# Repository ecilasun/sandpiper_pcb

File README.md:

## Sandpiper keyboard PCB and enclosure design files

This repo contains the PCB files for sandpiper project.

## Notes

- This PCB is optional and is not required to be able to run sandpiper. It merely contains a custom USB keyboard that fits into the provided enclosure.
- The enclosure is also optional. Sandpiper does not requre an enclosure to function and can be booted from pretty much any Xynq7020 board with 512Mbytes of memory, an etnernet and USB controller, plus some HDMI connector leading to the FPGA pins. For boards with more memory than 512Mbytes the device tree and SDK has to be updated to shift device addresses to the last 32Mbytes of memory. This also means th driver has to be rebuilt with those addresses (in the future driver will read them from the devic tree so there won't be a need to rebuild it)
- The enclosure is designed to be printed in one big piece for the top and bottom halves (plus the side connection pieces) Recommended material is PETG-strong as it is very unlikely to warp. Other materials might also work but print at your own risk or split the design manually, as there's no built-in measures in the design to avoid warping.
- Enclosure design requires solidworks connected, and the pcb design required KiCad 9 or above.
- If you intend to build a PCB yourself via online services (oshpark, jlcpcb etc) please note to match the parts to the ones listed as close as you can. Mismatches in part numbers might result in wrong pin connections.
- If you build the keyboard PCB and want to program the firmware on it, please see the firmware/ folder in this repo. Use an AVR programmer with AVRdude / AVRdudess or QMK Toolbox to burn the flash onto the chip.
- The pin header for the programmer goes on the bottom side of the board where the chip sits, and the square pin connection is actually the MISO pin and not the ground pin due to an error. Please see the following image to locate the correct pins and plug the programmer header accordingly:<br><br>
- Do not forget to cut or remove the programming header pins once you're done so that the board does not get stuck or bend when sliding it into the rails on the bottom side of the enclosure.

## Documentation

See the [Sandpiper project page](https://ecilasun.github.io/sandpiper/) for links to all related repositories and SDK documentation.

## Development toolchains

See the [Sandpiper project page](https://ecilasun.github.io/sandpiper/) for development toolchain setup instructions.

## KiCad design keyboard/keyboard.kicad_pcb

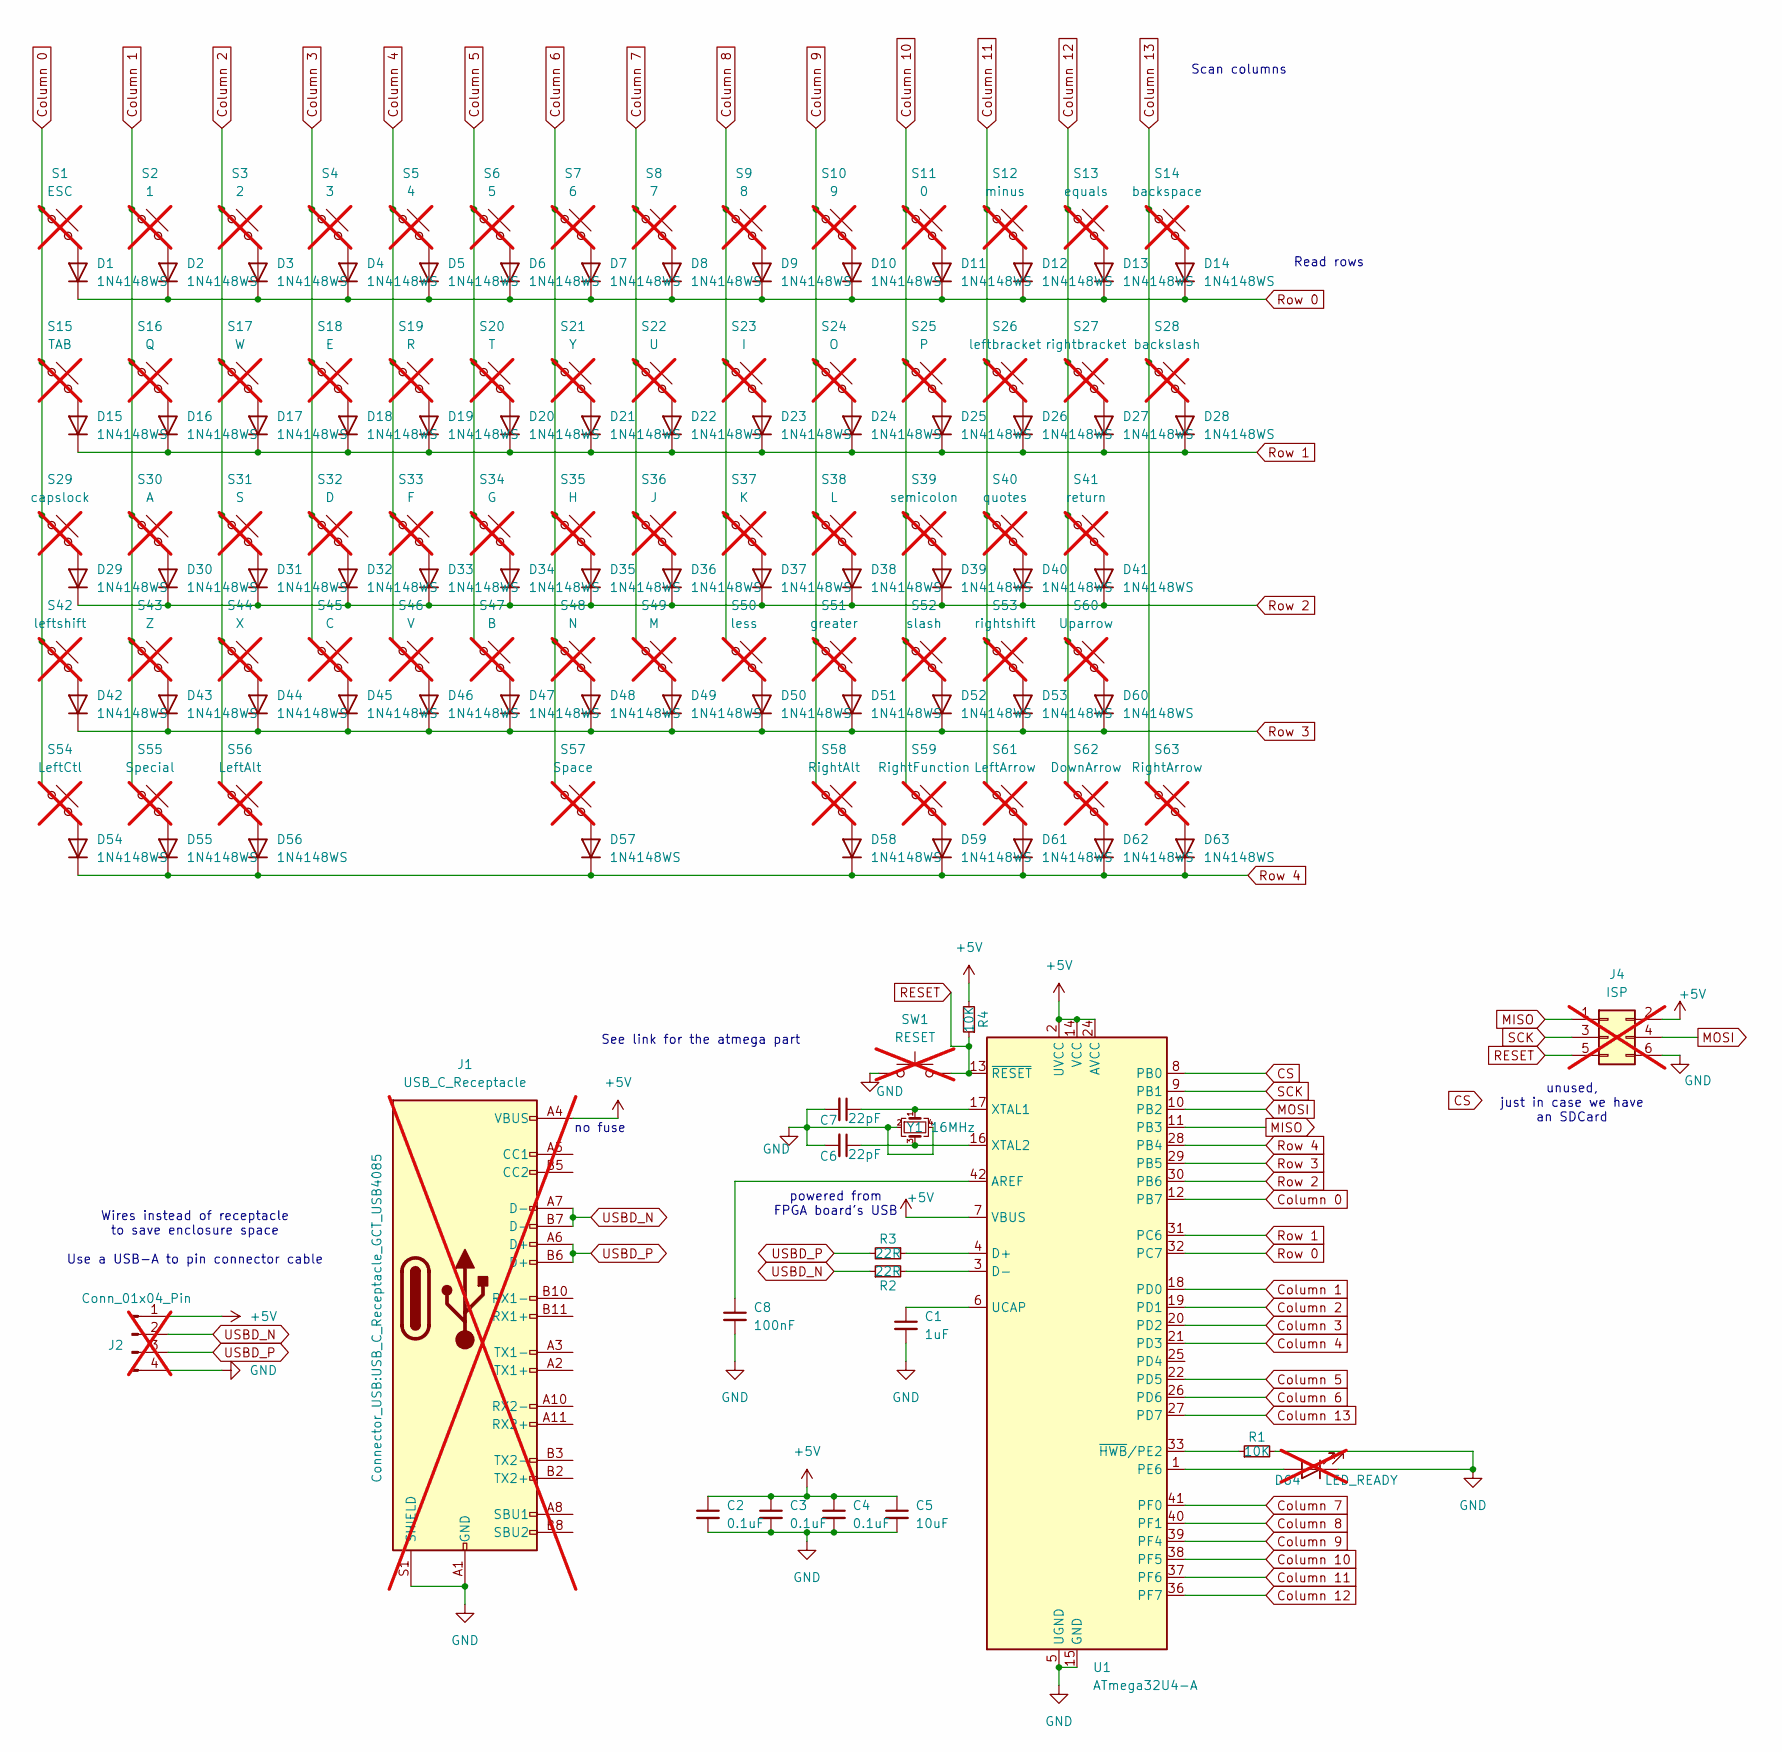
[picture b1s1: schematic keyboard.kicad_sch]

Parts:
C1: 1uF; C_0805_2012Metric
C2, C3, C4: 0.1uF; C_0805_2012Metric
C5: 10uF; C_0805_2012Metric
C6, C7: 22pF; C_0805_2012Metric
C8: 100nF; C_0805_2012Metric
D1, D2, D3, D4, D5, D6, D7, D8, D9, D10, D11, D12, D13, D14, D15, D16, D17, D18, D19, D20, D21, D22, D23, D24, D25, D26, D27, D28, D29, D30, D31, D32, D33, D34, D35, D36, D37, D38, D39, D40, D41, D42, D43, D44, D45, D46, D47, D48, D49, D50, D51, D52, D53, D54, D55, D56, D57, D58, D59, D60, D61, D62, D63: 1N4148WS‎; D_SOD-323_HandSoldering
D64: LED_READY; LED_1206_3216Metric; not fitted
J1: USB_C_Receptacle; USB_C_Receptacle_GCT_USB4085; not fitted
J2: Conn_01x04_Pin; PinHeader_1x04_P2.54mm_Vertical; not fitted
J4: ISP; PinHeader_2x03_P2.54mm_Vertical; not fitted
R1, R4: 10K; R_0805_2012Metric
R2, R3: 22R; R_0805_2012Metric
S1: ESC; SW_Cherry_MX_1.00u_PCB; not fitted
S2: 1; SW_Cherry_MX_1.00u_PCB; not fitted
S3: 2; SW_Cherry_MX_1.00u_PCB; not fitted
S4: 3; SW_Cherry_MX_1.00u_PCB; not fitted
S5: 4; SW_Cherry_MX_1.00u_PCB; not fitted
S6: 5; SW_Cherry_MX_1.00u_PCB; not fitted
S7: 6; SW_Cherry_MX_1.00u_PCB; not fitted
S8: 7; SW_Cherry_MX_1.00u_PCB; not fitted
S9: 8; SW_Cherry_MX_1.00u_PCB; not fitted
S10: 9; SW_Cherry_MX_1.00u_PCB; not fitted
S11: 0; SW_Cherry_MX_1.00u_PCB; not fitted
S12: minus; SW_Cherry_MX_1.00u_PCB; not fitted
S13: equals; SW_Cherry_MX_1.00u_PCB; not fitted
S14: backspace; SW_Cherry_MX_2.00u_PCB; not fitted
S15: TAB; SW_Cherry_MX_1.00u_PCB; not fitted
S16: Q; SW_Cherry_MX_1.00u_PCB; not fitted
S17: W; SW_Cherry_MX_1.00u_PCB; not fitted
S18: E; SW_Cherry_MX_1.00u_PCB; not fitted
S19: R; SW_Cherry_MX_1.00u_PCB; not fitted
S20: T; SW_Cherry_MX_1.00u_PCB; not fitted
S21: Y; SW_Cherry_MX_1.00u_PCB; not fitted
S22: U; SW_Cherry_MX_1.00u_PCB; not fitted
S23: I; SW_Cherry_MX_1.00u_PCB; not fitted
S24: O; SW_Cherry_MX_1.00u_PCB; not fitted
S25: P; SW_Cherry_MX_1.00u_PCB; not fitted
S26: leftbracket; SW_Cherry_MX_1.00u_PCB; not fitted
S27: rightbracket; SW_Cherry_MX_1.00u_PCB; not fitted
S28: backslash; SW_Cherry_MX_1.00u_PCB; not fitted
S29: capslock; SW_Cherry_MX_1.00u_PCB; not fitted
S30: A; SW_Cherry_MX_1.00u_PCB; not fitted
S31: S; SW_Cherry_MX_1.00u_PCB; not fitted
S32: D; SW_Cherry_MX_1.00u_PCB; not fitted
S33: F; SW_Cherry_MX_1.00u_PCB; not fitted
S34: G; SW_Cherry_MX_1.00u_PCB; not fitted
S35: H; SW_Cherry_MX_1.00u_PCB; not fitted
S36: J; SW_Cherry_MX_1.00u_PCB; not fitted
S37: K; SW_Cherry_MX_1.00u_PCB; not fitted
S38: L; SW_Cherry_MX_1.00u_PCB; not fitted
S39: semicolon; SW_Cherry_MX_1.00u_PCB; not fitted
S40: quotes; SW_Cherry_MX_1.00u_PCB; not fitted
S41: return; SW_Cherry_MX_2.25u_PCB; not fitted
S42: leftshift; SW_Cherry_MX_1.75u_PCB; not fitted
S43: Z; SW_Cherry_MX_1.00u_PCB; not fitted
S44: X; SW_Cherry_MX_1.00u_PCB; not fitted
S45: C; SW_Cherry_MX_1.00u_PCB; not fitted
S46: V; SW_Cherry_MX_1.00u_PCB; not fitted
S47: B; SW_Cherry_MX_1.00u_PCB; not fitted
S48: N; SW_Cherry_MX_1.00u_PCB; not fitted
S49: M; SW_Cherry_MX_1.00u_PCB; not fitted
S50: less; SW_Cherry_MX_1.00u_PCB; not fitted
S51: greater; SW_Cherry_MX_1.00u_PCB; not fitted
S52: slash; SW_Cherry_MX_1.00u_PCB; not fitted
S53: rightshift; SW_Cherry_MX_2.25u_PCB; not fitted
S54: LeftCtl; SW_Cherry_MX_1.25u_PCB; not fitted
S55: Special; SW_Cherry_MX_1.00u_PCB; not fitted
S56: LeftAlt; SW_Cherry_MX_1.25u_PCB; not fitted
S57: Space; SW_Cherry_MX_6.25u_PCB; not fitted
S58: RightAlt; SW_Cherry_MX_1.25u_PCB; not fitted
S59: RightFunction; SW_Cherry_MX_1.00u_PCB; not fitted
S60: Uparrow; SW_Cherry_MX_1.00u_PCB; not fitted
S61: LeftArrow; SW_Cherry_MX_1.00u_PCB; not fitted
S62: DownArrow; SW_Cherry_MX_1.00u_PCB; not fitted
S63: RightArrow; SW_Cherry_MX_1.00u_PCB; not fitted
SW1: RESET; SW_Tactile_SPST_NO_Straight_CK_PTS636Sx25SMTRLFS; not fitted
U1: ATmega32U4-A; TQFP-44_10x10mm_P0.8mm
Y1: 16MHz; Crystal_SMD_3225-4Pin_3.2x2.5mm

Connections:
+5V: C2.1, C3.1, C4.1, C5.1, J1.A4 (VBUS), J1.A9 (VBUS), J1.B4 (VBUS), J1.B9 (VBUS), J2.1, J4.2, R4.2, U1.2 (UVCC), U1.7 (VBUS), U1.14 (VCC), U1.24 (AVCC), U1.34 (VCC), U1.44 (AVCC)
CS: U1.8 (PB0)
Column 0: S1.1, S15.1, S29.1, S42.1, S54.1, U1.12 (PB7)
Column 1: S2.1, S16.1, S30.1, S43.1, S55.1, U1.18 (PD0)
Column 2: S3.1, S17.1, S31.1, S44.1, S56.1, U1.19 (PD1)
Column 3: S4.1, S18.1, S32.1, S45.1, U1.20 (PD2)
Column 4: S5.1, S19.1, S33.1, S46.1, U1.21 (PD3)
Column 5: S6.1, S20.1, S34.1, S47.1, U1.22 (PD5)
Column 6: S7.1, S21.1, S35.1, S48.1, S57.1, U1.26 (PD6)
Column 7: S8.1, S22.1, S36.1, S49.1, U1.41 (PF0)
Column 8: S9.1, S23.1, S37.1, S50.1, U1.40 (PF1)
Column 9: S10.1, S24.1, S38.1, S51.1, S58.1, U1.39 (PF4)
Column 10: S11.1, S25.1, S39.1, S52.1, S59.1, U1.38 (PF5)
Column 11: S12.1, S26.1, S40.1, S53.1, S61.1, U1.37 (PF6)
Column 12: S13.1, S27.1, S41.1, S60.1, S62.1, U1.36 (PF7)
Column 13: S14.1, S28.1, S63.1, U1.27 (PD7)
GND: C1.2, C2.2, C3.2, C4.2, C5.2, C6.2, C7.2, C8.2, D64.1 (K), J1.A1 (GND), J1.A12 (GND), J1.B1 (GND), J1.B12 (GND), J1.S1 (SHIELD), J2.4, J4.6, R1.2, SW1.1, U1.5 (UGND), U1.15 (GND), U1.23 (GND), U1.35 (GND), U1.43 (GND), Y1.2, Y1.4
MISO: J4.1, U1.11 (PB3)
MOSI: J4.4, U1.10 (PB2)
unnamed: D1.2 (A), S1.2
unnamed: D2.2 (A), S2.2
unnamed: D3.2 (A), S3.2
unnamed: D4.2 (A), S4.2
unnamed: D5.2 (A), S5.2
unnamed: D6.2 (A), S6.2
unnamed: D7.2 (A), S7.2
unnamed: D8.2 (A), S8.2
unnamed: D9.2 (A), S9.2
unnamed: D10.2 (A), S10.2
unnamed: D11.2 (A), S11.2
unnamed: D12.2 (A), S12.2
unnamed: D13.2 (A), S13.2
unnamed: D14.2 (A), S14.2
unnamed: D15.2 (A), S15.2
unnamed: D16.2 (A), S16.2
unnamed: D17.2 (A), S17.2
unnamed: D18.2 (A), S18.2
unnamed: D19.2 (A), S19.2
unnamed: D20.2 (A), S20.2
unnamed: D21.2 (A), S21.2
unnamed: D22.2 (A), S22.2
unnamed: D23.2 (A), S23.2
unnamed: D24.2 (A), S24.2
unnamed: D25.2 (A), S25.2
unnamed: D26.2 (A), S26.2
unnamed: D27.2 (A), S27.2
unnamed: D28.2 (A), S28.2
unnamed: D29.2 (A), S29.2
unnamed: D30.2 (A), S30.2
unnamed: D31.2 (A), S31.2
unnamed: D32.2 (A), S32.2
unnamed: D33.2 (A), S33.2
unnamed: D34.2 (A), S34.2
unnamed: D35.2 (A), S35.2
unnamed: D36.2 (A), S36.2
unnamed: D37.2 (A), S37.2
unnamed: D38.2 (A), S38.2
unnamed: D39.2 (A), S39.2
unnamed: D40.2 (A), S40.2
unnamed: D41.2 (A), S41.2
unnamed: D42.2 (A), S42.2
unnamed: D43.2 (A), S43.2
unnamed: D44.2 (A), S44.2
unnamed: D45.2 (A), S45.2
unnamed: D46.2 (A), S46.2
unnamed: D47.2 (A), S47.2
unnamed: D48.2 (A), S48.2
unnamed: D49.2 (A), S49.2
unnamed: D50.2 (A), S50.2
unnamed: D51.2 (A), S51.2
unnamed: D52.2 (A), S52.2
unnamed: D53.2 (A), S53.2
unnamed: D54.2 (A), S54.2
unnamed: D55.2 (A), S55.2
unnamed: D56.2 (A), S56.2
unnamed: D57.2 (A), S57.2
unnamed: D58.2 (A), S58.2
unnamed: D59.2 (A), S59.2
unnamed: D60.2 (A), S60.2
unnamed: D61.2 (A), S61.2
unnamed: D62.2 (A), S62.2
unnamed: D63.2 (A), S63.2
unnamed: D64.2 (A), U1.1 (PE6)
unnamed: C8.1, U1.42 (AREF)
unnamed: R3.1, U1.4 (D+)
unnamed: R2.2, U1.3 (D-)
unnamed: C1.1, U1.6 (UCAP)
unnamed: C7.1, U1.17 (XTAL1), Y1.1
unnamed: C6.1, U1.16 (XTAL2), Y1.3
unnamed: R1.1, U1.33 (~HWB/PE2)
RESET: J4.5, R4.1, SW1.2, U1.13 (~RESET)
Row 0: D1.1 (K), D2.1 (K), D3.1 (K), D4.1 (K), D5.1 (K), D6.1 (K), D7.1 (K), D8.1 (K), D9.1 (K), D10.1 (K), D11.1 (K), D12.1 (K), D13.1 (K), D14.1 (K), U1.32 (PC7)
Row 1: D15.1 (K), D16.1 (K), D17.1 (K), D18.1 (K), D19.1 (K), D20.1 (K), D21.1 (K), D22.1 (K), D23.1 (K), D24.1 (K), D25.1 (K), D26.1 (K), D27.1 (K), D28.1 (K), U1.31 (PC6)
Row 2: D29.1 (K), D30.1 (K), D31.1 (K), D32.1 (K), D33.1 (K), D34.1 (K), D35.1 (K), D36.1 (K), D37.1 (K), D38.1 (K), D39.1 (K), D40.1 (K), D41.1 (K), U1.30 (PB6)
Row 3: D42.1 (K), D43.1 (K), D44.1 (K), D45.1 (K), D46.1 (K), D47.1 (K), D48.1 (K), D49.1 (K), D50.1 (K), D51.1 (K), D52.1 (K), D53.1 (K), D60.1 (K), U1.29 (PB5)
Row 4: D54.1 (K), D55.1 (K), D56.1 (K), D57.1 (K), D58.1 (K), D59.1 (K), D61.1 (K), D62.1 (K), D63.1 (K), U1.28 (PB4)
SCK: J4.3, U1.9 (PB1)
USBD_N: J1.A7 (D-), J1.B7 (D-), J2.2, R2.1
USBD_P: J1.A6 (D+), J1.B6 (D+), J2.3, R3.2

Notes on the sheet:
Scan columns
no fuse
unused, just in case we have an SDCard
Wires instead of receptacle to save enclosure space Use a USB-A to pin connector cable
See link for the atmega part
powered from FPGA board's USB
Read rows

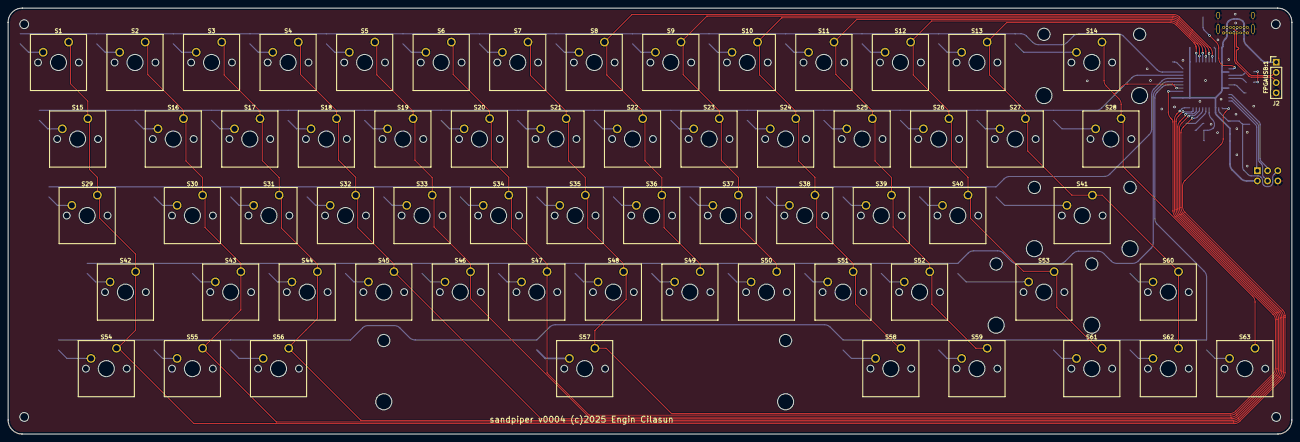
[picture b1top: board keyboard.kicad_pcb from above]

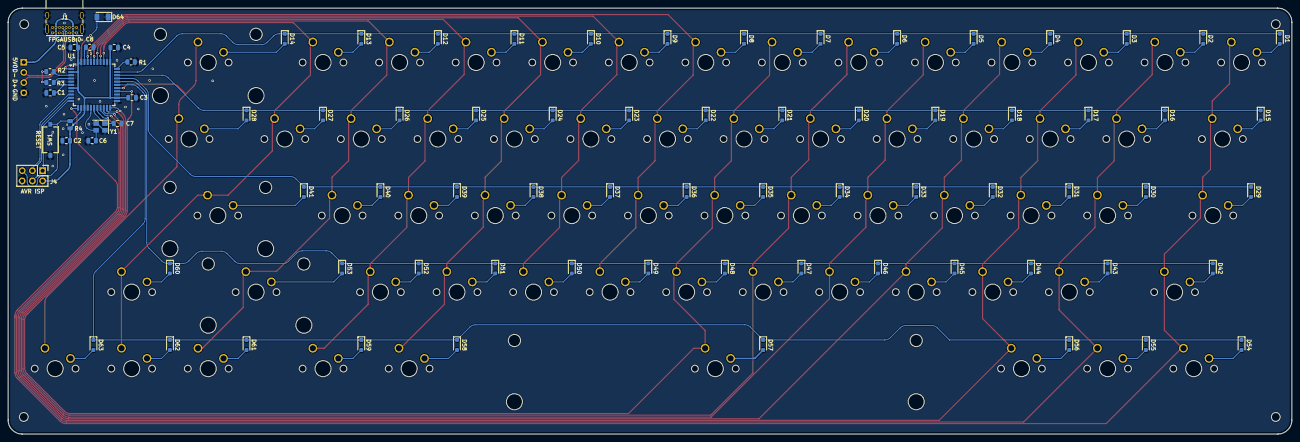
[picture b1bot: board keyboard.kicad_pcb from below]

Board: 2 copper layers, 319.5 x 106.0 mm, 145 parts (81 on the bottom side), 98 nets.

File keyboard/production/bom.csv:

Designator,Footprint,Quantity,Value,LCSC Part #
C1,0805,1,1uF,
"C2, C3, C4",0805,3,0.1uF,
C5,0805,1,10uF,
"C6, C7",0805,2,22pF,
C8,0805,1,100nF,
"D1, D10, D11, D12, D13, D14, D15, D16, D17, D18, D19, D2, D20, D21, D22, D23, D24, D25, D26, D27, D28, D29, D3, D30, D31, D32, D33, D34, D35, D36, D37, D38, D39, D4, D40, D41, D42, D43, D44, D45, D46, D47, D48, D49, D5, D50, D51, D52, D53, D54, D55, D56, D57, D58, D59, D6, D60, D61, D62, D63, D7, D8, D9",D_SOD-323_HandSoldering,63,1N4148WS‎,
"R1, R4",0805,2,10K,
"R2, R3",0805,2,22R,
U1,TQFP-44_10x10mm_P0.8mm,1,ATmega32U4-A,
Y1,Crystal_SMD_3225-4Pin_3.2x2.5mm,1,16MHz,

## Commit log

2025-05-06 initial submit
2025-05-06 Updated with reference switches
2025-05-06 Updated mechanical bits
2025-05-29 USB keyboard instead
2025-06-01 updated pcb and enclosure
2025-06-05 Updated keyboard with fixes, also much smaller
2025-06-08 Updated enclousre
2025-06-09 Added default firmware and layout for keyboard
2025-06-10 Updated keyboard layout and firmware Typing this from the new keyboard :)
2025-06-10 More fixes to the keyboard pcb
2025-06-13 Updated keyboard layout
2025-06-13 removed unnecessary file
2025-06-14 Updated PCB layout, added caps
2025-06-19 PCB update
2025-06-24 More compact enclosure
2025-06-28 Updatd enclosure
2025-06-28 More updates to the enclousre
2025-07-05 Updated enclosure
2025-08-03 Added a smaller enclosure option
2025-08-06 New enclosure work
2025-08-07 Enclosure 2 fixes
2025-08-10 Removed old enclosure
2025-08-18 New enclousre and fix for PCB
2025-08-23 enclosure and pcb fixes
2025-08-30 Minor touchup
2025-08-30 Tidy up
2025-08-31 Updating documentation
2025-08-31 Forgotten info
2025-09-05 Updates to enclosure (snap hooks and detail fixes)
2025-10-17 Enclosure update
2025-11-18 Update README with related repositories
    Added related repositories for SDK and build files.
2025-11-21 Updated layout
2025-11-28 Updates to enclosure design
2025-11-29 Update for cable
2025-12-06 Enclosure updates
2025-12-22 Typos

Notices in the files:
keyboard/keyboard.kicad_pcb:
sandpiper v0004 (c)2025 Engin Cilasun
